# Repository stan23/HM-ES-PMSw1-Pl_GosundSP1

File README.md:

# HM-ES-PMSw1-Pl_GosundSP1          

Patrick hat eine [verbesserte Version gemacht](https://github.com/der-pw/HM-ES-PMSw1-Pl_GosundSP1).

Umbau [Gosund SP1 bzw. BliTZWOLF SHP2](https://www.blitzwolf.com/Wifi-Smart-Socket-EU-p-244.html) zu HM-ES-PMSw1-Pl_SP1

Dies basiert auf der hervorragenden Arbeit von [pa-pa](https://github.com/pa-pa/AskSinPP) und [Jérôme](https://github.com/jp112sdl/Beispiel_AskSinPP).

*Achtung*: es kann verschiedene Versionen der Gosund/Blitzwolf-Stecker geben. Diese Platine passt bei folgender Version:

# Hardware

### Bauteile

#### Reichelt

[Bestellliste](https://www.reichelt.de/my/1519439)

Bauteil                  | Bestellnummer   | Anzahl | Kommentar
------------------------ | --------------- | ------ | ---------
C1                       | X5R-G0603 10/6  |   1    | -
C2 .. C6                 | X7R-G0603 100N  |   5    | -
R1                       | RND 0603 1 10K  |   1    | -
R2                       | RND 0603 1 1,0M |   1    | -
U1                       | ATMEGA 644PA-AU |   1    | -
Y1                       | CSTCE 8,00      |   1    | -
Verbinder zu U2          | MPE 156-1-032   |   1    | muss per Hand umgebogen werden
Verbinder zu U2          | SL 1X20G 2,00   |   1    | optional, hilfreich zum Anschließen des ISP

#### Sonstiges

Bauteil | Bestellnummer            | Anzahl | Kommentar
------- | ------------------------ | ------ | ---------
U2      | CC1101 Funkmodul 868 MHz |   1    | z.B. [eBay](https://www.ebay.de/itm/272455136087)

~8,3 cm Draht als Antenne

### Programmieradapter
- 1x ISP (z.B. [diesen hier](https://www.diamex.de/dxshop/USB-ISP-Programmer-fuer-Atmel-AVR-Rev2))

# Software

### Fuses
Ext:  0xFF
High: 0xD2
Low:  0xFF (für den internen Takt: 0xE2)

`C:\Program Files (x86)\Arduino\hardware\tools\avr\bin> .\avrdude -C ..\etc\avrdude.conf -p m644p -P com7 -c stk500 -U lfuse:w:0xFF:m -U hfuse:w:0xD2:m -U efuse:w:0xFF:m`

### Firmware

Projektverzeichnis: [HM-ES-PMSw1-Pl_GosundSP1](https://github.com/jp112sdl/Beispiel_AskSinPP/tree/master/examples/HM-ES-PMSw1-Pl_GosundSP1)

Benötigt werden die Bibliotheken [AskSinPP](https://github.com/pa-pa/AskSinPP) aus dem master-Branch, sowie die [HLW8012](https://github.com/xoseperez/hlw8012), die [MightyCore](https://github.com/MCUdude/MightyCore), die [EnableInterrupt](https://github.com/GreyGnome/EnableInterrupt) und [Low-Power](https://github.com/rocketscream/Low-Power).

# Bauanleitung

Zuerst den ATmega auflöten, die Markierung (kleiner Punkt) muss zur Beschriftung U1 zeigen.
Danach die Kondensatoren und den Widerstand auflöten.

Mit einem Multimeter messen ob kein Kurzschluss zwischen VCC und GND besteht (mehrere 10 K Widerstand sind okay).

Den ISP Programmieradapter an die Lötaugen des CC1101 anschließen. Ein Adapterkabel vom 6-poligen ISP-Adapter auf eine 2 mm-Stiftleiste wird empfohlen :)

Pin am ISP-Kabel | Bedeutung
---------------- | ----------
1                | MISO
2                | VCC
3                | SCK
4                | MOSI
5                | Reset
6                | GND

Anschließend kann das Funkmodul auf der Rückseite aufgelötet werden. Dabei gibt es verschiedene Möglichkeiten:
- mit Stift- und Buchsenleiste (abnehmbar)
- mit Stiftleiste

An den Antennenanschluss muss noch das 8,3 cm Drahtstück angelötet werden.

Mit einem FTDI USB-seriell-Adapter an den Lötpunkten RX, TX, 3.3 V und GND und mit einem Terminalprogramm kann man die Ausgabe beobachten. Es sollten schon *Ignore...*-Meldungen empfangen und angezeigt werden.

Als nächstes muss das überflüssige WLAN-Modul aus dem Gosund/Blitzwolf-Stecker ausgelötet und die neue Platine eingelötet werden. Der Antennendraht muss mit Heißkleber im Gehäuse befestigt werden, so dass er möglichst weit von 230 V entfernt ist!

Nach dem Zusammenbau kann der Anlernvorgang durch langes Drücken der einzigen Taste gestartet werden. Die Anlernprozedur wird durch langsames Blinken der blauen WLAN-LED angezeigt, der Erfolg durch schnelles Blinken.

# Kalibrierung

TBD

# Bilder

Dieses Werk ist lizenziert unter einer [Creative Commons Namensnennung - Nicht-kommerziell - Weitergabe unter gleichen Bedingungen 4.0 International Lizenz](http://creativecommons.org/licenses/by-nc-sa/4.0/).

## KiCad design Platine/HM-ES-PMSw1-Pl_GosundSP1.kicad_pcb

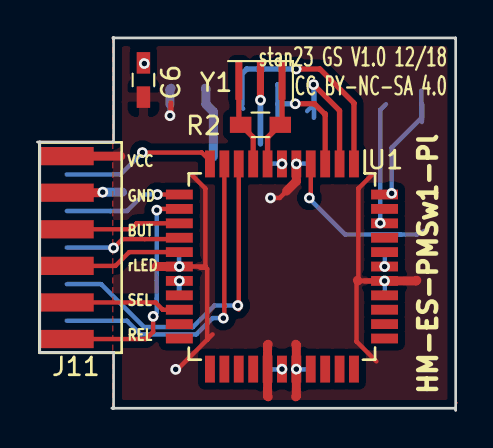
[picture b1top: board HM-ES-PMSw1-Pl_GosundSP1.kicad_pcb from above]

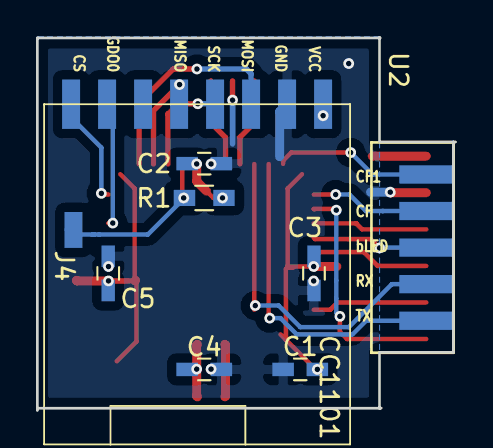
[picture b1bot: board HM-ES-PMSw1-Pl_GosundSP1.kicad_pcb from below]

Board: 2 copper layers, 23.2 x 20.6 mm, 13 parts (8 on the bottom side), 19 nets.

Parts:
C1: 10u; C_0603_HandSoldering
C2, C3, C4, C5, C6: 100n; C_0603_HandSoldering
J4: Reset; Testpad
J11: BW_Gosund_Con; Gosund_SP1-C_V2.3
R1: 10k; R_0603_HandSoldering
R2: 1M; R_0603_HandSoldering
U1: ATMEGA644PA-AU; TQFP-44_10x10mm_Pitch0.8mm
U2: CC1101; CC1101_SMD
Y1: Resonator; Resonator_SMD_muRata_TPSKA-3pin_7.9x3.8mm_HandSoldering

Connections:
/BUTTON: J11.BUT, U1.14
/CF: J11.CF, U1.12
/CF1: J11.CF1, U1.11
/CS: U1.44, U2.8
/GDO0: U1.42, U2.7
/LED_blue: J11.bLED, U1.15
/LED_red: J11.rLED, U1.16
/MISO: U1.2, U2.5
/MOSI: U1.1, U2.3
/RELAY: J11.REL, U1.13
/RESET: J4.1, R1.2, U1.4
/RX: J11.RX, U1.9
/SCK: U1.3, U2.4
/SEL: J11.SEL, U1.20
/TX: J11.TX, U1.10
GND: C1.2, C2.2, C3.2, C4.2, C5.2, C6.2, J11.GND, U1.6, U1.18, U1.28, U1.39, U2.2, Y1.2
unnamed: R2.1, U1.7, Y1.1
unnamed: R2.2, U1.8, Y1.3
VCC: C1.1, C2.1, C3.1, C4.1, C5.1, C6.1, J11.VCC, R1.1, U1.5, U1.17, U1.27, U1.29, U1.38, U2.1

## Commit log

2018-10-10 add schematic and KiCad project
2018-10-11 change name
2018-10-11 rename KiCad files to reflect new repo name
2018-10-12 update schematic
2018-10-19 oard V0.1 routing complete
2018-10-22 fix wrong Paste layer in connetor
2018-11-01 update documentation and add pictures
2018-11-04 add resonator for better clock
    e.g. CSTCE8M00G55-R0, available at Reichelt (CSTCE 8,00)
2018-11-10 finalize V1.0
    fix #1, #2, #4
2018-11-10 Update README.md
    add resonator and 1M resistor to BOM
2018-12-02 add more pictures
2018-12-21 Support for Gosund SP1 V2.3 (new WiFi module)
2018-12-31 fix wrong blue LED and button for Gosund SP1 V2.3
2021-01-24 link to der-pw's fork

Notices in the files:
Platine/HM-ES-PMSw1-Pl_GosundSP1.kicad_pcb:
CC BY-NC-SA 4.0
README.md:
License: CC BY-NC-SA 4.0
Creative Commons Lizenzvertrag
